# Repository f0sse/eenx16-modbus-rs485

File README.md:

Projektfiler för kandidatarbetet "Demand Side Flexibility in Electrical Heating Systems" på Chalmers 2024.

# Modbus

I detta träd finns ritningar och kod för en Raspberry Pi 4 HAT ämnad att prata
Modbus över RS485.

## Raspberry Pi 4

Lägg till följande i filen `/boot/config.txt`, under taggen `[pi4]`:

	dtoverlay=disable-bt
	dtoverlay=uart4,ctsrts
	dtparam=uart0=off
	dtparam=uart1=off
	enable_uart=0

Kör `systemctl disable hciuart` som root.

I filen `/boot/cmdline.txt`, se till att ta bort alla boot consoles som
refererar till `ttyAMA*`, och se till att raden innehåller
`plymouth.ignore-serial-consoles`.

För att dubbelkolla att hardware flow control är på för uart4, kör
`raspi-gpio get 8-11` och kolla att följande tabell stämmer.

| Funktion | GPIO | Pin |
|---------:|:----:|:---:|
|       TX |   8  |  24 |
|       RX |   9  |  21 |
|      CTS |  10  |  19 |
|      RTS |  11  |  23 |

## HAT

För att samla in data från de tre elmätarna i labbet, använder vi oss av en
egen-designad Raspberry Pi-HAT, som sköter seriell kommunikation med en[MAX483]
(https://www.analog.com/en/products/max483.html) och temperaturläsningar med
en [DS18B20](https://www.analog.com/en/products/ds18b20.html) (monterad på en
extern modul).

För att prata Modbus användes [libmodbus](https://libmodbus.org) och ett eget
program skrivet i C för att samla in momentan och total effekt för samtliga
faser på de tre elmätarna i interval om 5 sekunder, och skicka dessa data till
en tidsseriedatabas.

Alla design-filer finns under `/hat`.

## Misc

MAX483 gör det möjligt för oss att kommunicera enligt RS-485, men chippet kräver
att man sätter pinnarna 2-3 höga vid Tx och låga vid Rx.

Problemet med RPI var att en vanlig UART endast har pinnar för Rx/Tx, och inga
möjligheter att automatiskt kontrollera de nödvändiga pinnarna på något sätt.

Lyckligtvis har RPI 4 möjlgheter till hardware flow control, så den pinne man
sätter som Request To Send (RTS) kan användas till att sätta pinnarna 2-3
istället för det tänkta användningsområdet. Libmodbus var också skrivet runt
denna tanken för dess RTU-driver. På så vis kan man använda RPI  4 och uppåt,
och prata Modbus med endast dess UART.

`influx.c` innehåller ett mindre polerat bibliotek för att skriva mätdata till
[InfluxDB](https://www.influxdata.com) genom biblioteket [CURL](https://curl.se).

`modbus.c` använder libmodbus för att fråga tre olika
elmätare om fasvärden för spänning, ström, aktiv effekt och så vidare. För mer
information om vilka register som används, se manualen som ligger i mappen
`doc`.

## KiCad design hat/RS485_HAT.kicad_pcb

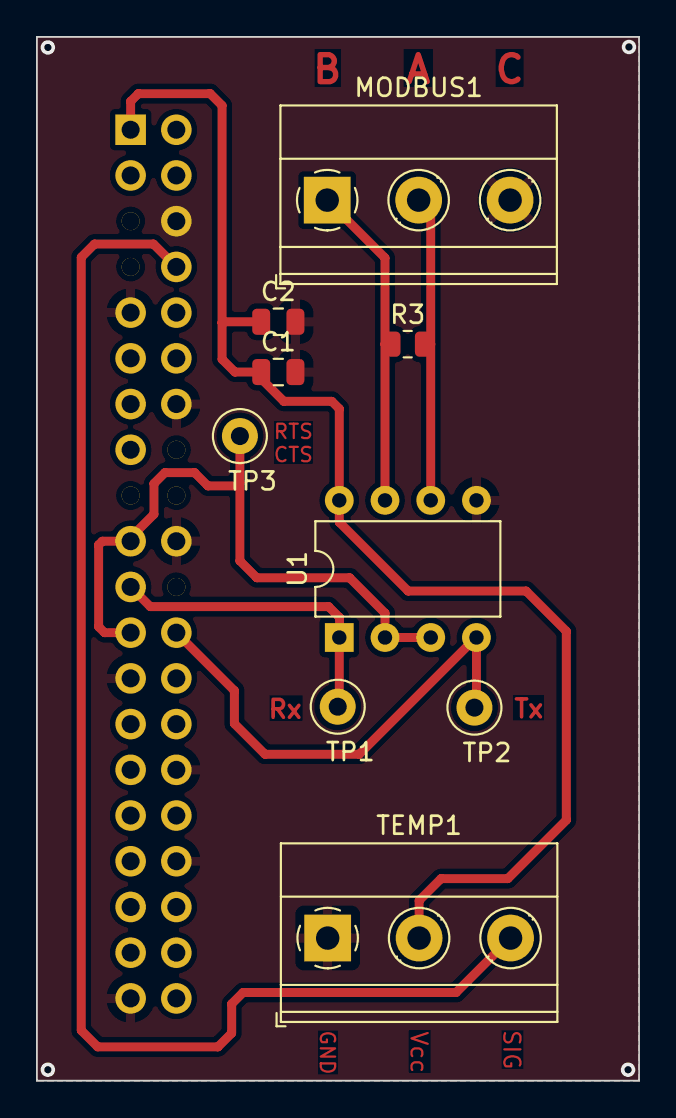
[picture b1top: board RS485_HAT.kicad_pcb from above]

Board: 2 copper layers, 33.5 x 58.0 mm, 10 parts (1 on the bottom side), 8 nets.

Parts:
C1: 10 uF; C_0805_2012Metric
C2: 100 nF; C_0805_2012Metric
J1: Raspberry_Pi_2_3; PinSocket_2x20_P2.54mm_Vertical
MODBUS1: Screw_Terminal_01x03; TerminalBlock_Phoenix_MKDS-1,5-3-5.08_1x03_P5.08mm_Horizont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
R3: 120 Ω; R_0805_2012Metric
TEMP1: Screw_Terminal_01x03; TerminalBlock_Phoenix_MKDS-1,5-3-5.08_1x03_P5.08mm_Horizont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
TP1: Rx; TestPoint_Loop_D1.80mm_Drill1.0mm_Beaded
TP2: Tx; TestPoint_Loop_D1.80mm_Drill1.0mm_Beaded
TP3: RTS/CTS; TestPoint_Loop_D1.80mm_Drill1.0mm_Beaded
U1: MAX483E; DIP-8_W7.62mm

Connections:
/SIG: J1.8 (GPIO14/TXD), TEMP1.3
GND: C1.2, C2.2, J1.6 (GND), J1.9 (GND), J1.14 (GND), J1.20 (GND), J1.25 (GND), J1.30 (GND), J1.34 (GND), J1.39 (GND), MODBUS1.3, TEMP1.1, U1.5 (GND)
unnamed: J1.21 (MISO0/GPIO9), TP1.1, U1.1 (RO)
unnamed: J1.19 (MOSI0/GPIO10), J1.23 (SCLK0/GPIO11), TP3.1, U1.2 (~RE), U1.3 (DE)
unnamed: J1.24 (~CE0/GPIO8), TP2.1, U1.4 (DI)
unnamed: MODBUS1.1, R3.1, U1.7 (B)
unnamed: MODBUS1.2, R3.2, U1.6 (A)
VCC: C1.1, C2.1, J1.1 (3V3), J1.17 (3V3), TEMP1.2, U1.8 (VCC)

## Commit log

2024-05-08 publikation av kod
2024-05-08 README.md
2024-05-08 added copyright notice
